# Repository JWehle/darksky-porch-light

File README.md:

# darksky-porch-light
A custom DarkSky friendly porch light that adjusts its brightness based on ambient conditions.

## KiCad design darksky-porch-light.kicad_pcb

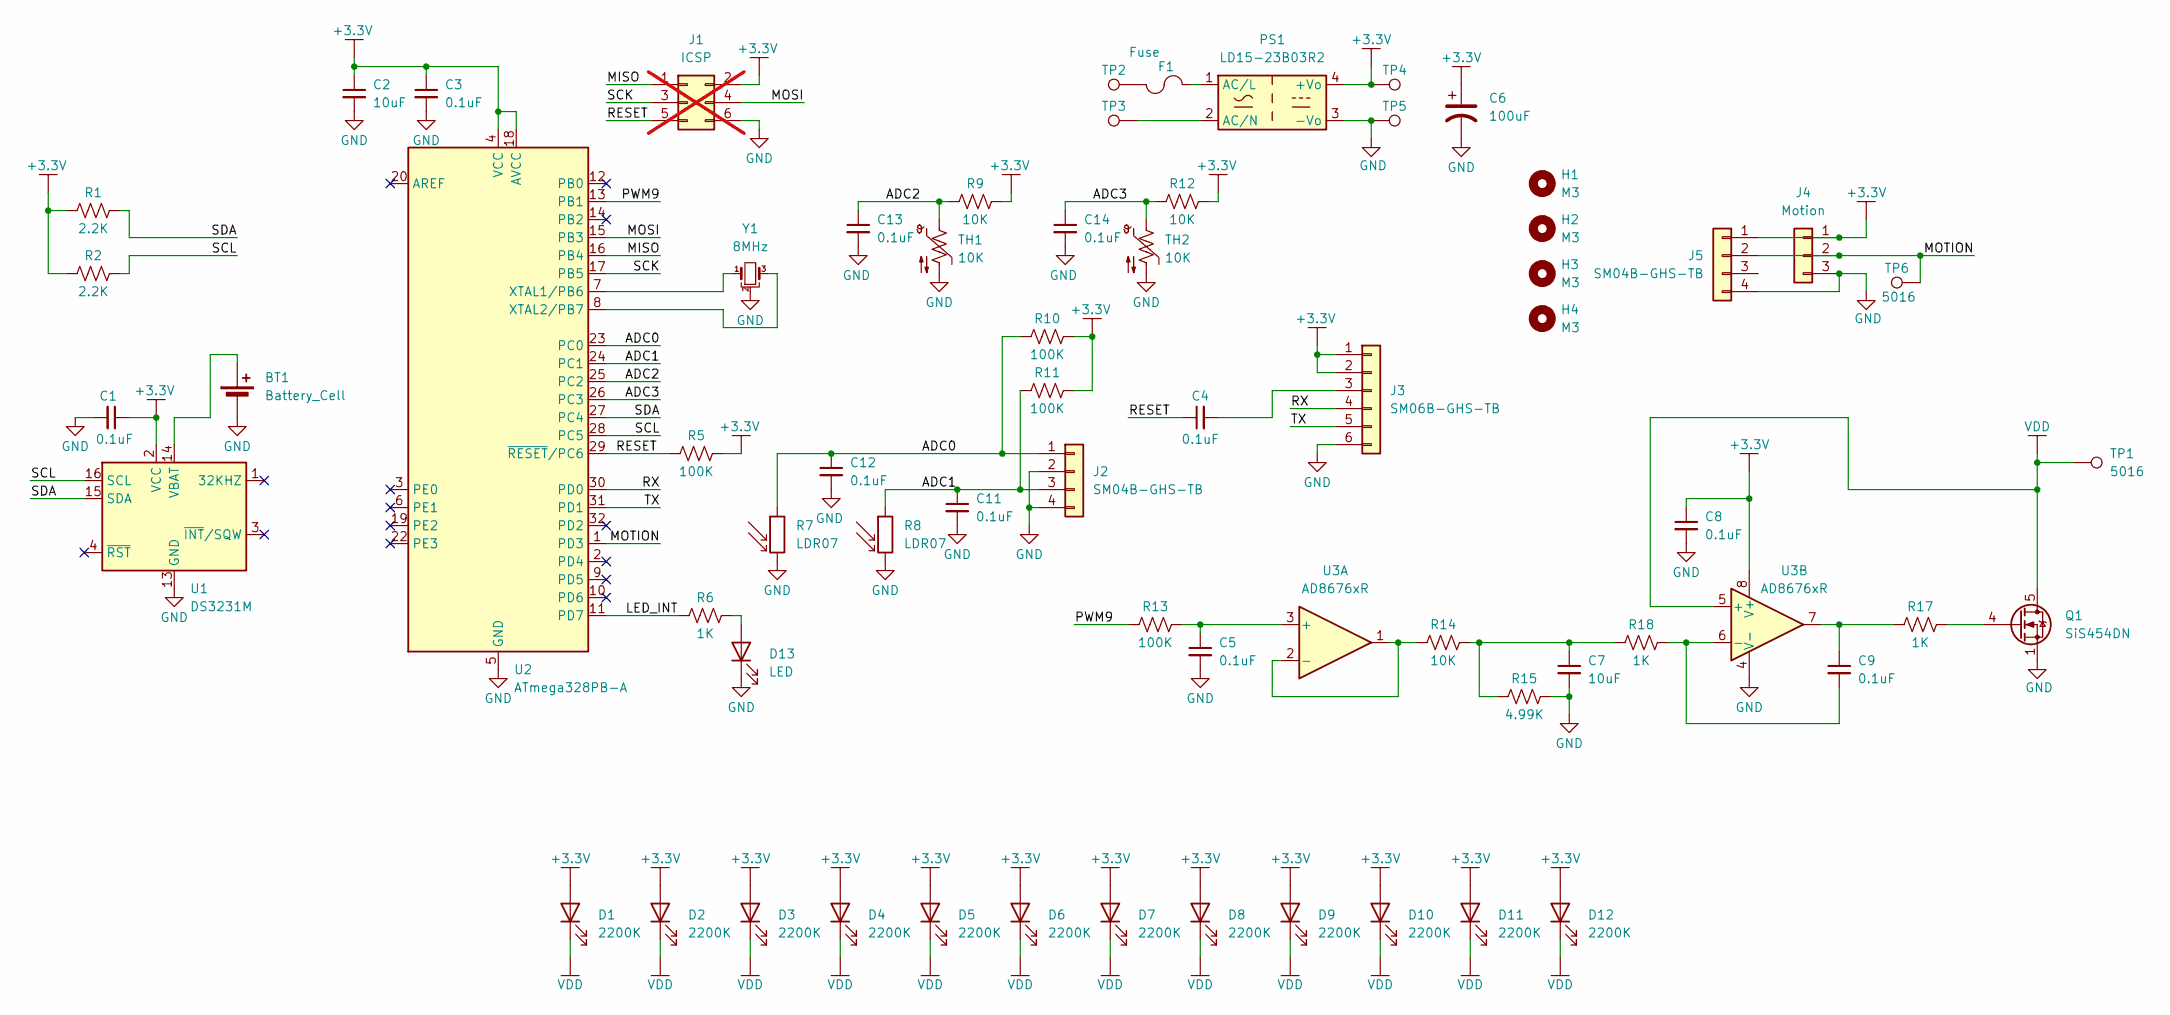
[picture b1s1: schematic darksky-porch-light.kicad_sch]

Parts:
BT1: Battery_Cell; BatteryHolder_Keystone_3002_1x2032
C1, C3, C4, C5, C8, C9, C11, C12, C13, C14: 0.1uF; C_0603_1608Metric
C2, C7: 10uF; C_0603_1608Metric
C6: 100uF; CP_Elec_6.3x5.4_Nichicon
D1, D2, D3, D4, D5, D6, D7, D8, D9, D10, D11, D12: 2200K; LED_PLCC_2835_Handsoldering
D13: LED; LED_0603_1608Metric_Pad1.05x0.95mm_HandSolder
F1: Fuse; Fuseholder_Littelfuse_Nano2_154x
H1, H2, H3, H4: M3; MountingHole_3.2mm_M3
J1: ICSP; PinSocket_2x03_P2.00mm_Vertical; not fitted
J2, J5: SM04B-GHS-TB; JST_GH_SM04B-GHS-TB_1x04-1MP_P1.25mm_Horizontal
J3: SM06B-GHS-TB; JST_GH_SM06B-GHS-TB_1x06-1MP_P1.25mm_Horizontal
J4: Motion; PinSocket_1x03_P2.54mm_Vertical
PS1: LD15-23B03R2; LD15-23BxxR2_MNS
Q1: SiS454DN; Vishay_PowerPAK_1212-8_Single
R1, R2: 2.2K; R_0603_1608Metric
R5, R10, R11, R13: 100K; R_0603_1608Metric
R6, R17, R18: 1K; R_0603_1608Metric
R7, R8: LDR07; R_LDR_5.1x4.3mm_P3.4mm_Vertical
R9, R12, R14: 10K; R_0603_1608Metric
R15: 4.99K; R_0603_1608Metric
TH1, TH2: 10K; R_0603_1608Metric
TP1: 5016; TestPoint_Keystone_5016_Vias
TP2, TP3, TP4, TP5: TestPoint; TestPoint_Keystone_5016_Vias
TP6: 5016; TestPoint_Keystone_5016_Compact
U1: DS3231M; SOIC-16W_7.5x10.3mm_P1.27mm
U2: ATmega328PB-A; TQFP-32_7x7mm_P0.8mm
U3: AD8676xR; SOIC-8_3.9x4.9mm_P1.27mm
Y1: 8MHz; Resonator_SMD_Murata_CSTxExxV-3Pin_3.0x1.1mm_HandSoldering

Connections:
+3.3V: C1.1, C2.1, C3.1, C6.1, C8.1, D1.2 (A), D2.2 (A), D3.2 (A), D4.2 (A), D5.2 (A), D6.2 (A), D7.2 (A), D8.2 (A), D9.2 (A), D10.2 (A), D11.2 (A), D12.2 (A), J1.2, J3.1, J3.2, J4.1, J5.1, PS1.4 (+Vo), R1.1, R2.1, R5.2, R9.2, R10.2, R11.2, R12.2, TP4.1, U1.2 (VCC), U2.4 (VCC), U2.18 (AVCC), U3.8 (V+)
/ADC0: C12.1, J2.1, R7.1, R10.1, U2.23 (PC0)
/ADC1: C11.1, J2.3, R8.1, R11.1, U2.24 (PC1)
/ADC2: C13.1, R9.1, TH1.1, U2.25 (PC2)
/ADC3: C14.1, R12.1, TH2.1, U2.26 (PC3)
/LED_INT: R6.1, U2.11 (PD7)
/MISO: J1.1, U2.16 (PB4)
/MOSI: J1.4, U2.15 (PB3)
/MOTION: J4.2, J5.2, TP6.1, U2.1 (PD3)
/PWM9: R13.1, U2.13 (PB1)
/RESET: C4.1, J1.5, R5.1, U2.29 (~RESET/PC6)
/RX: J3.4, U2.30 (PD0)
/SCK: J1.3, U2.17 (PB5)
/SCL: R2.2, U1.16 (SCL), U2.28 (PC5)
/SDA: R1.2, U1.15 (SDA), U2.27 (PC4)
/TX: J3.5, U2.31 (PD1)
GND: BT1.2 (-), C1.2, C2.2, C3.2, C5.2, C6.2, C7.2, C8.2, C11.2, C12.2, C13.2, C14.2, D13.1 (K), J1.6, J2.2, J2.4, J3.6, J4.3, J5.4, PS1.3 (-Vo), Q1.1 (S), Q1.2 (S), Q1.3 (S), R7.2, R8.2, R15.2, TH1.2, TH2.2, TP5.1, U1.5 (GND), U1.6 (GND), U1.7 (GND), U1.8 (GND), U1.9 (GND), U1.10 (GND), U1.11 (GND), U1.12 (GND), U1.13 (GND), U2.5 (GND), U2.21 (GND), U3.4 (V-), Y1.2
unnamed: BT1.1 (+), U1.14 (VBAT)
unnamed: C7.1, R14.2, R15.1, R18.1
unnamed: C9.1, R17.1, U3.7
unnamed: D13.2 (A), R6.2
unnamed: F1.1, TP2.1
unnamed: C4.2, J3.3
unnamed: F1.2, PS1.1 (AC/L)
unnamed: PS1.2 (AC/N), TP3.1
unnamed: Q1.4 (G), R17.2
unnamed: U2.7 (XTAL1/PB6), Y1.1
unnamed: U2.8 (XTAL2/PB7), Y1.3
unnamed: C5.1, R13.2, U3.3 (+)
unnamed: R14.1, U3.1, U3.2 (-)
unnamed: C9.2, R18.2, U3.6 (-)
VDD: D1.1 (K), D2.1 (K), D3.1 (K), D4.1 (K), D5.1 (K), D6.1 (K), D7.1 (K), D8.1 (K), D9.1 (K), D10.1 (K), D11.1 (K), D12.1 (K), Q1.5 (D), TP1.1, U3.5 (+)

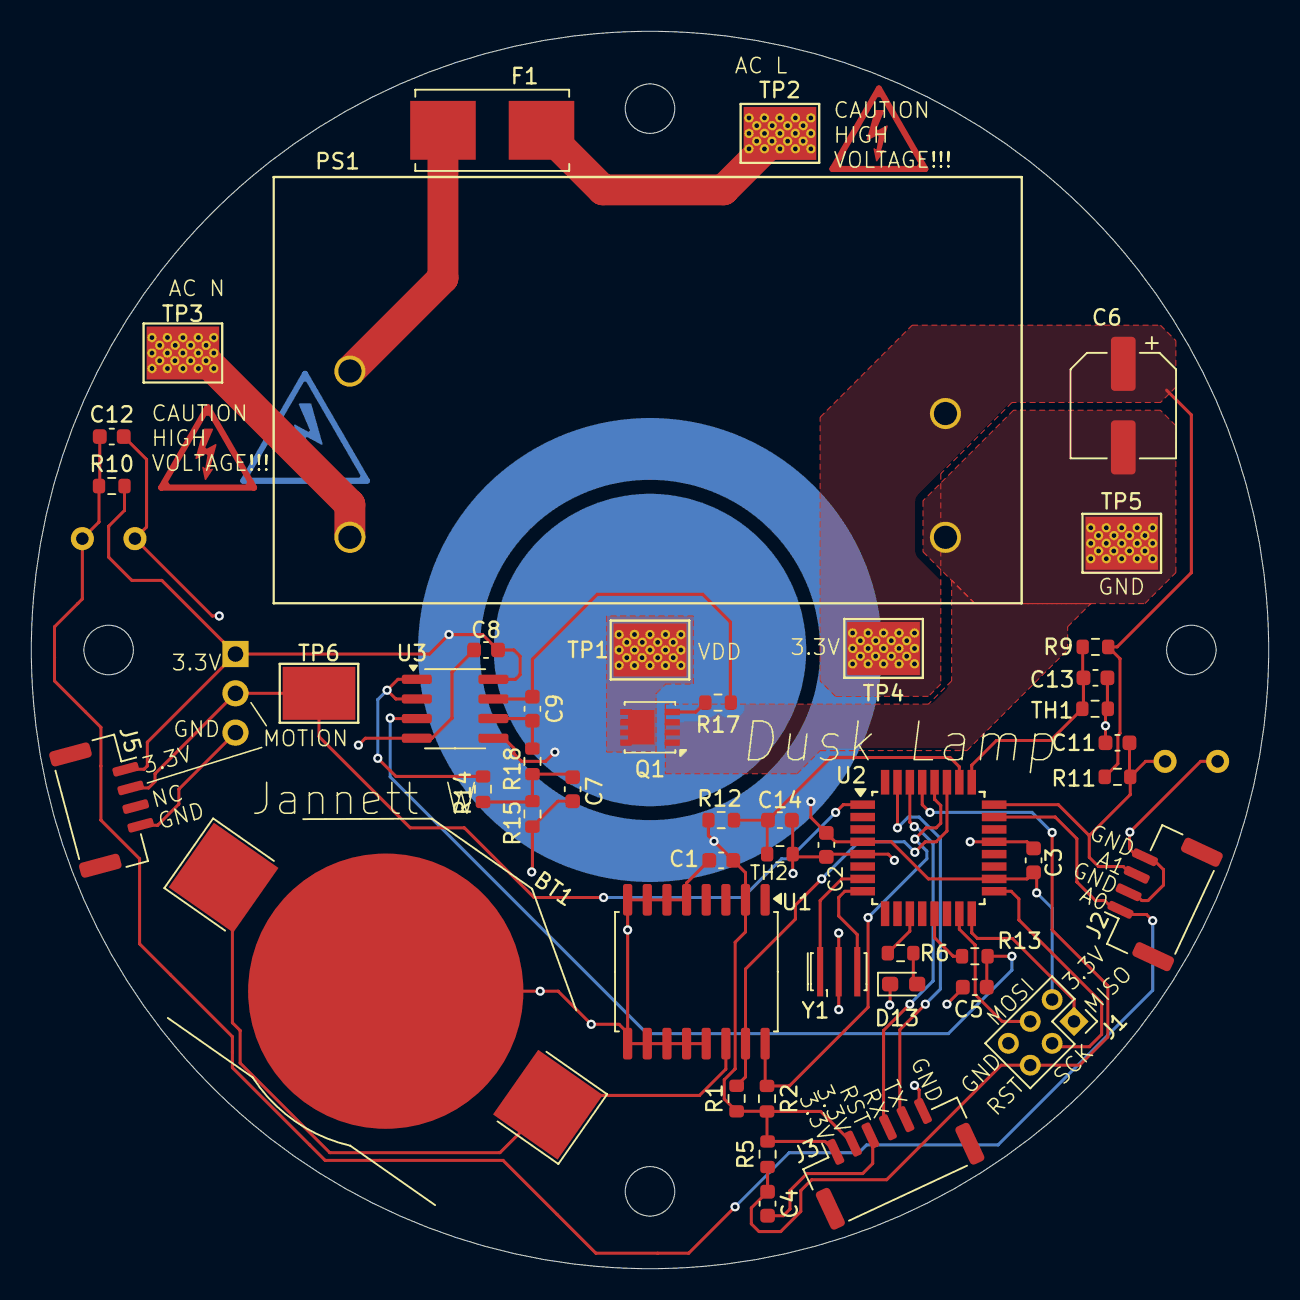
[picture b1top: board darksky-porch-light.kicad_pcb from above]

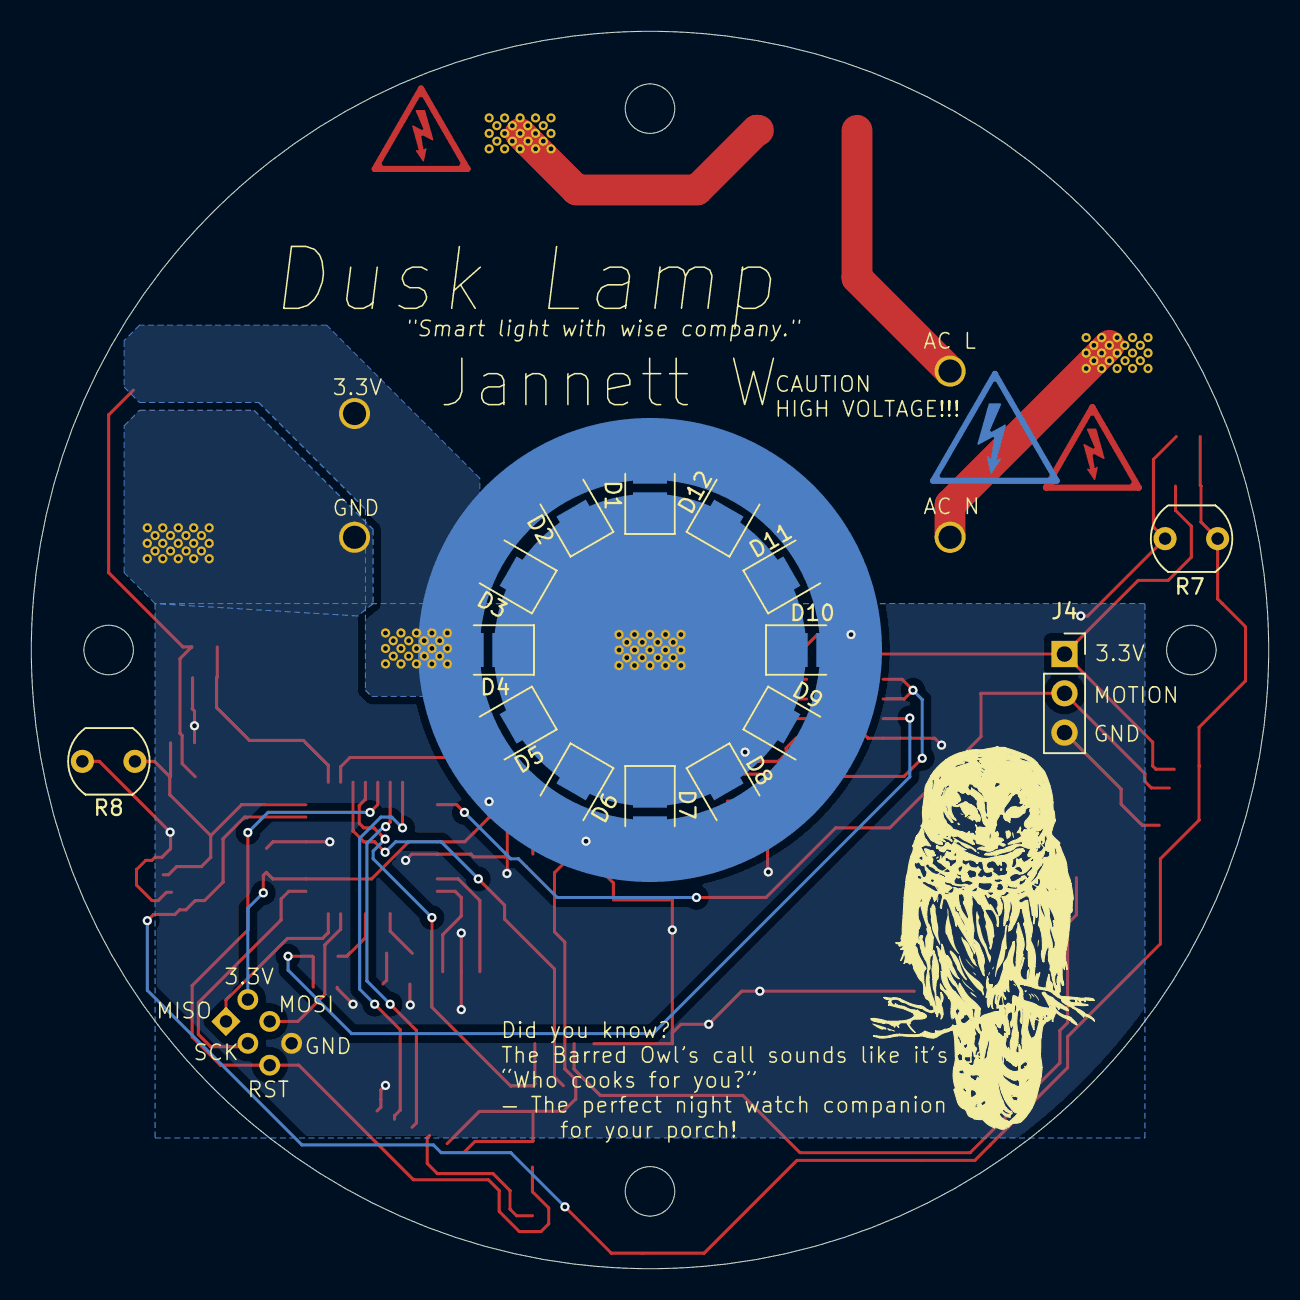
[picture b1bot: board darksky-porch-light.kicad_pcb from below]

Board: 2 copper layers, 80.0 x 80.0 mm, 66 parts (15 on the bottom side), 32 nets.

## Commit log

2025-06-16 initial commit
    starting the proj
2025-06-16 start on sch
2025-06-29 layout
2025-06-29 done
